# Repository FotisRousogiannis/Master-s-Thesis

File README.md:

# Master-s-Thesis
DEVELOPMENT OF ROBOTIC ARM AND INDEGRATION OF COMPUTER VISION METHODS

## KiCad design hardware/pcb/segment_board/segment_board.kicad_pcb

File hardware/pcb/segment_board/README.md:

# Segment board v1 (KiCad 10)

Κοινή πλακέτα τμήματος του βραχίονα — προδιαγραφή: [`SPEC.md`](SPEC.md), BOM/διαθεσιμότητα: [`bom/`](bom/).

## Άνοιγμα
Άνοιξε το `segment_board.kicad_pro` στο **KiCad 10** (το PCB είναι αποθηκευμένο σε μορφή KiCad 10· το σχηματικό παράγεται σε μορφή KiCad 7). **Κλείσε το KiCad πριν από `git pull`**, αλλιώς το KiCad ξαναγράφει τις παλιές ρυθμίσεις του project πάνω στις νέες.
Τα project libraries `segment_board` δηλώνονται στο `sym-lib-table` (σύμβολα, `lib/segment_board.kicad_sym`) και στο
`fp-lib-table` (footprints, `lib/segment_board.pretty`).

## Το σχηματικό παράγεται από κώδικα
Όλο το κύκλωμα ορίζεται στο `gen/build.py`. **Μην** αλλάζεις συνδέσεις στο KiCad — άλλαξε το `build.py` και ξαναπαράγε:
```bash
cd gen && python3 build.py
kicad-cli sch export netlist -o /tmp/board.net ../segment_board.kicad_sch && python3 check_netlist.py /tmp/board.net
```
Ελεύθερα στο KiCad: μετακίνηση/τακτοποίηση συμβόλων για αναγνωσιμότητα (θα χαθεί αν ξαναπαραχθεί), layout PCB.

| Φύλλο | Περιεχόμενο |
|---|---|
| `power` | XT30 7.4 V, ασφάλεια, προστασία πολικότητας, TVS, eFuse TPS259827, INA219 · MSTB 5.1 V, eFuse TPS259472A · ιδανικές δίοδοι, buck 3.3 V · LED τροφοδοσίας |
| `mcu` | ESP32-S3-WROOM-1, USB-C + ESD, RESET/BOOT, LED κατάστασης, header GPIO |
| `i2c` | jumpers επιλογής master, PCA9685, TCA9548A, ADS1115, pull-ups, header επέκτασης |
| `connectors` | 9 servo, 6 encoders, 2 αφής (MCV 3.5 mm), ανίχνευση σύνδεσης με LM339 + 17 LED |
| `pi_link` | header Raspberry Pi, UART/EN/BOOT Pi↔ESP32, RS-485 THVD1451 + LINK, οπές στερέωσης |

## Footprints του project (`gen/footprints.py` → `lib/segment_board.pretty`)
| Footprint | Εξάρτημα | Πηγή |
|---|---|---|
| `TI_RGE0024_2EP` | TPS259827 (VQFN-24 4×4, 2 thermal pads, θερμικά vias 0.2 mm) | TI RGE0024M land pattern (tps25982.pdf σ. 55–57) |
| `TI_RPW0010A` | TPS259472A (VQFN-HR-10 2×2, γωνιακά pads σε σχήμα L) | TI RPW0010A land pattern (tps25947.pdf σ. 72–74) |
| `L_4x4mm_SMNR4020` | πηνίο buck 2.2 µH 3.4 A (LCSC C135262) | land pattern LCSC |
| `RPi_Socket_2x20_FaceDown` | header Pi με **κατοπτρικές στήλες** (Pi ανάποδα) + περίγραμμα Pi 4/5 και οπές M2.5 στο User.Drawings | ίδιο με το `Raspberry_Pi_Zero_Socketed_THT_FaceDown` του KiCad |

## PCB (`segment_board.kicad_pcb`)
Δημιουργήθηκε με `python3 gen/pcb.py --force` (με **αυτόματη αρχική τοποθέτηση**: κάθε chip μαζί με τα μικρά εξαρτήματα που μοιράζονται σήμα μαζί του, ανά περιοχή) (δεν ξανατρέχει χωρίς `--force`, για να μη χαθεί δουλειά). Από εκεί
και πέρα το layout γίνεται στο KiCad. Αλλαγές του σχηματικού περνούν με **Tools → Update PCB from Schematic (F8)**.

- 100 × 120 mm, 4 στρώσεις: F.Cu σήματα · In1 **GND** (zone) · In2 τροφοδοσίες · B.Cu σήματα
- Κανόνες JLCPCB και net classes: `python3 gen/rules.py` (ασφαλές να ξανατρέξει)

  | Net class | Δίκτυα | Πλάτος | Γιατί |
  |---|---|---|---|
  | Power_Servo | `VS_*`, `VSERVO` | 2.5 mm (+ πολύγωνα) | έως ~10 A |
  | Servo_Ch | `SERVO*_GND` | 1.0 mm | επιστροφή servo, έως ~4 A στο μπλοκάρισμα |
  | Power_Logic | 5 V, 3.3 V, GND | 0.6 mm | |
  | Default | σήματα | 0.2 mm | |
- **Πρόταση τοποθέτησης** (μετακινείται ελεύθερα): connectors αριστερά σε 4 στήλες (έξω από το Pi, τα φις μπαίνουν
  από πάνω), Pi ανάποδα στο δεξί μισό με τις θύρες του στην κάτω άκρη, κεραία ESP32 στην πάνω άκρη (έξω από το Pi,
  με το keep-out του footprint), XT30 και MSTB στην πάνω άκρη, USB-C στη δεξιά άκρη. Τα υπόλοιπα εξαρτήματα είναι
  δίπλα στην πλακέτα, ομαδοποιημένα ανά φύλλο του σχηματικού.
- Κάτω από το Pi (≥ 18 mm ελεύθερο ύψος): μόνο SMD.
- Το CI (KiCad 10) τρέχει **DRC** με έλεγχο ισοτιμίας με το σχηματικό και βγάζει εικόνες της πλακέτας.

## Υλικά (`bom/`)
- `parts.csv`: κύρια εξαρτήματα · `passives.csv`: αντιστάσεις, πυκνωτές, LED κ.λπ. — επιλογή με `resolve_passives.py`
  (προτίμηση σε **basic** parts της JLC, χωρίς χρέωση setup). Το `build.py` βάζει τους κωδικούς LCSC στο σχηματικό.
- Χωρίς LCSC (κόλληση με το χέρι): connectors MCV/MSTB/XT30, header Pi, pin headers/jumpers, θήκη ασφάλειας.

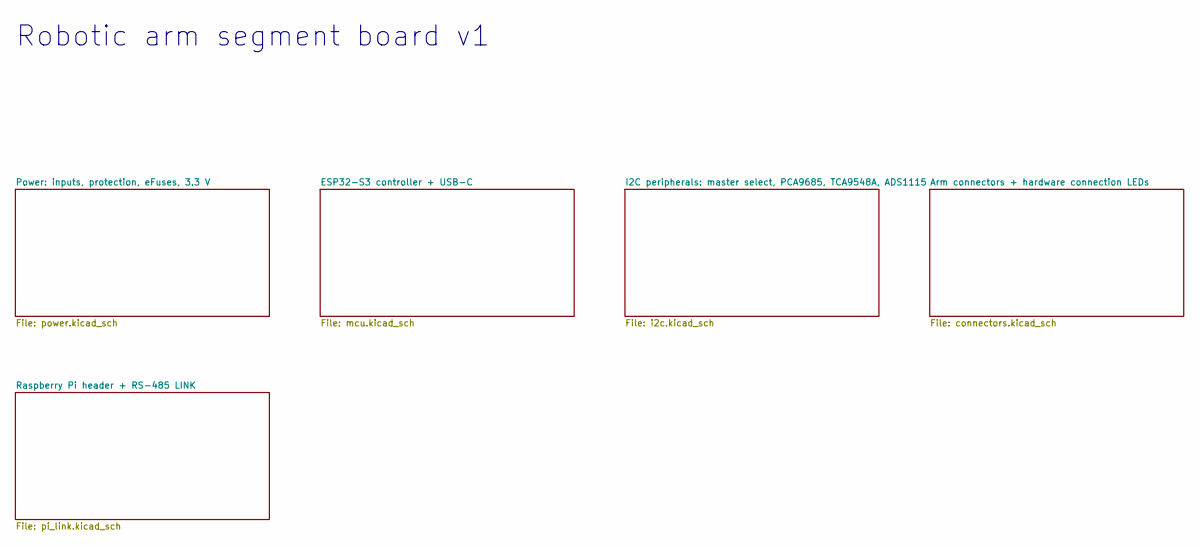
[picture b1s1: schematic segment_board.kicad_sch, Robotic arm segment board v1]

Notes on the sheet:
Robotic arm segment board v1

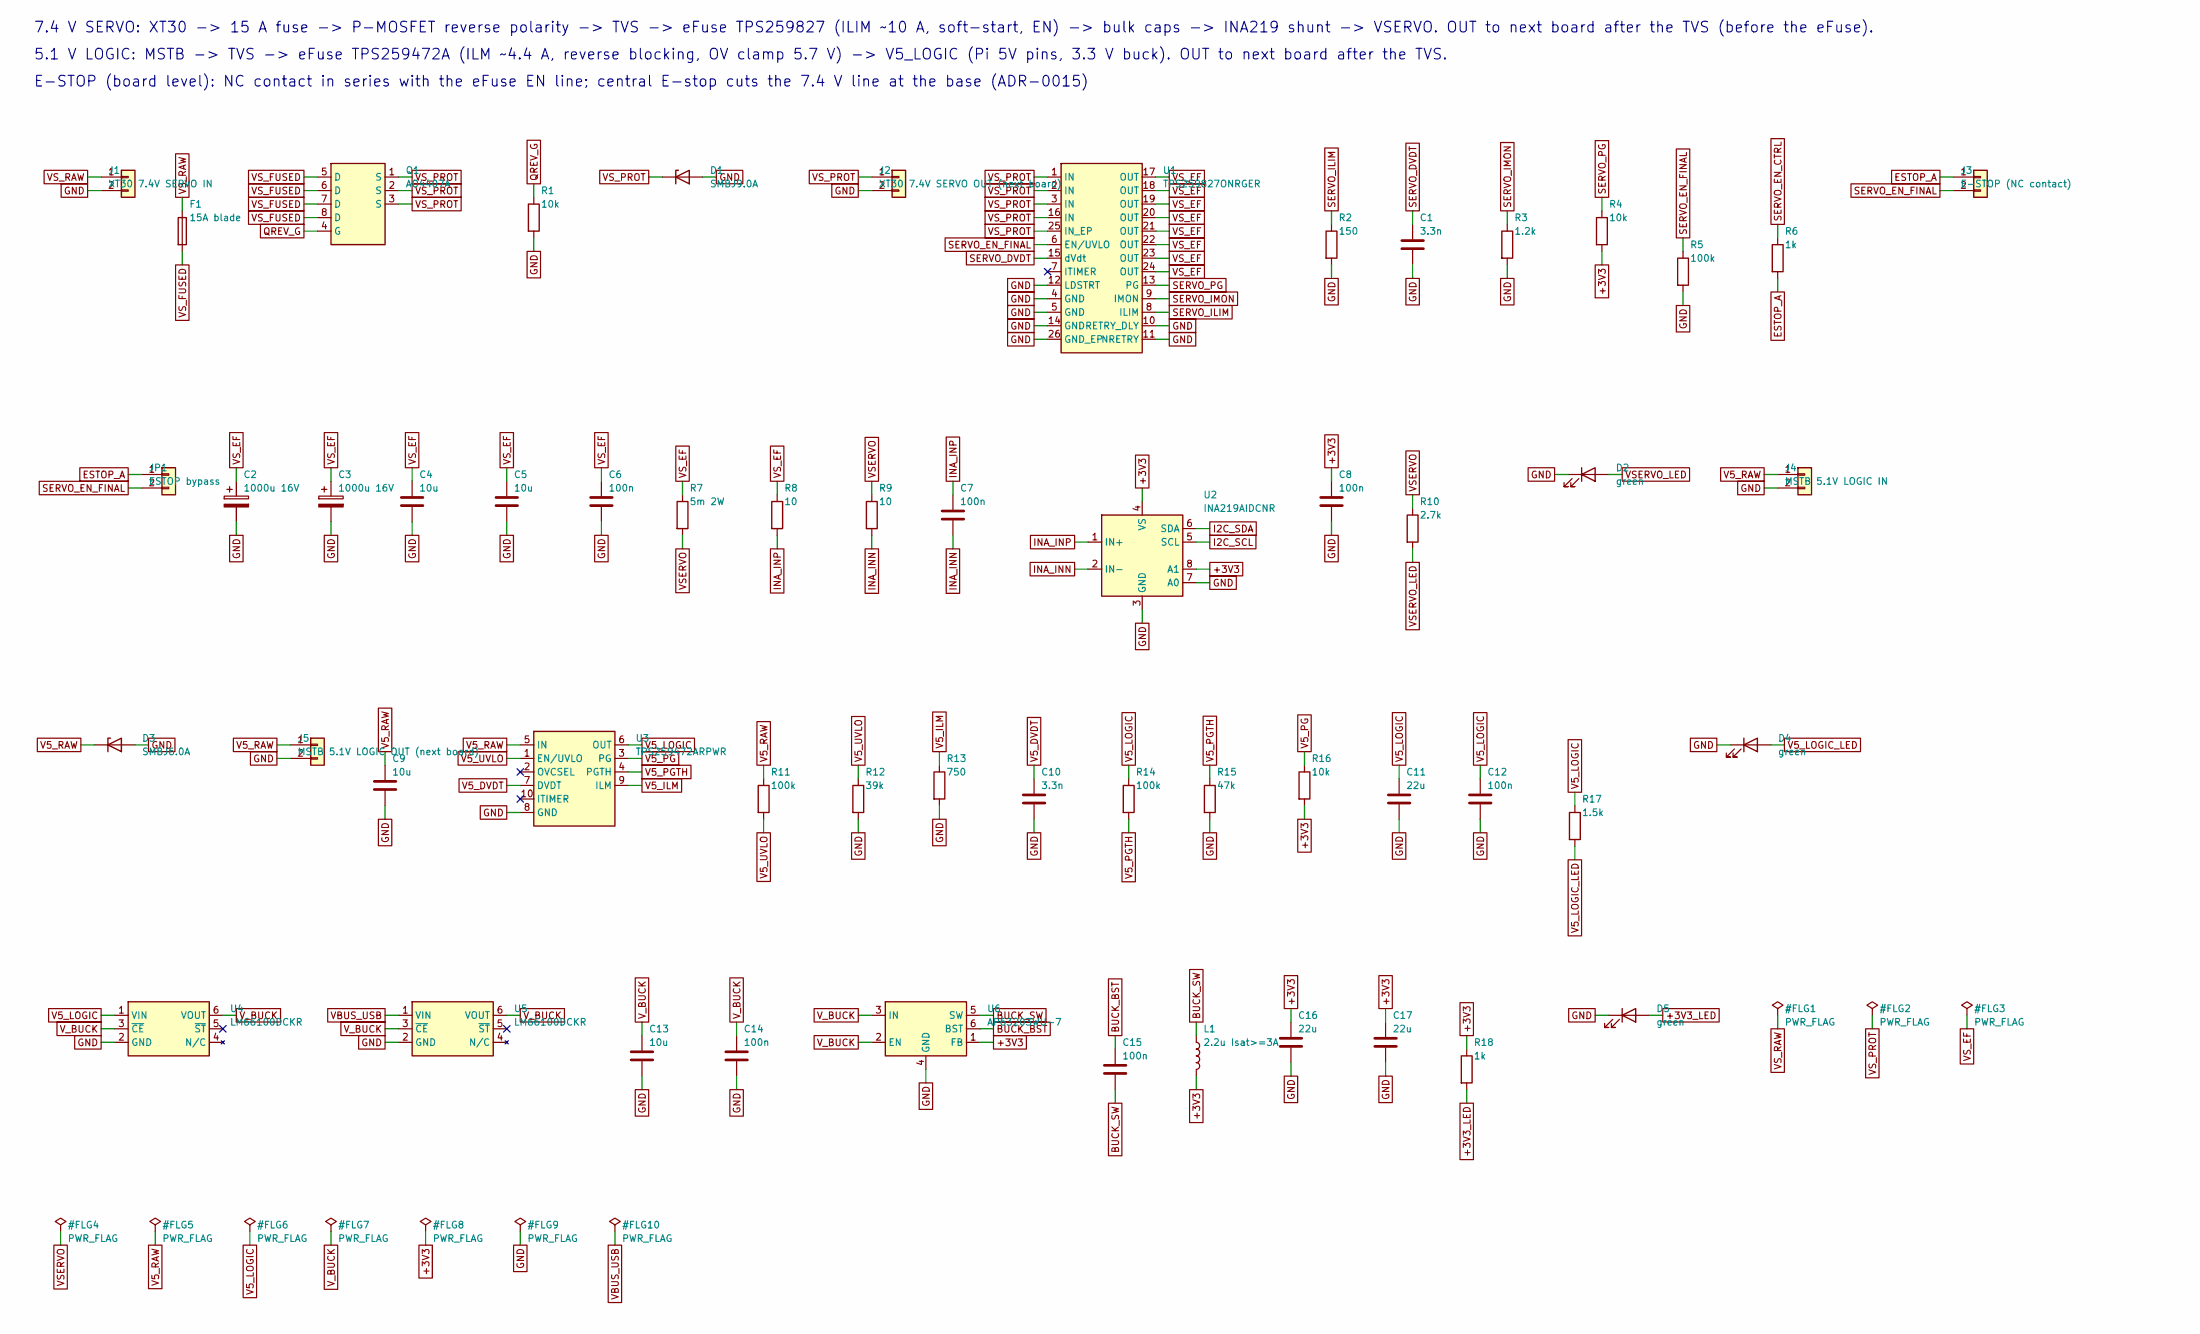
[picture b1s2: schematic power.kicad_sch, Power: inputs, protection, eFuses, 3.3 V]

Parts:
C1, C10: 3.3n; C_0402_1005Metric; LCSC C26404
C2, C3: 1000u 16V; CP_Radial_D10.0mm_P5.00mm; LCSC C88777
C4, C5, C9, C13: 10u; C_0805_2012Metric; LCSC C15850
C6, C7, C8, C12, C14, C15: 100n; C_0402_1005Metric; LCSC C1525
C11, C16, C17: 22u; C_0805_2012Metric; LCSC C45783
D1: SMBJ9.0A; D_SMB; LCSC C152088
D2, D4, D5: green; LED_0603_1608Metric; LCSC C2986030
D3: SMBJ6.0A; D_SMB; LCSC C19077560
F1: 15A blade; Fuseholder_Blade_Mini_Keystone_3568
J1: XT30 7.4V SERVO IN; AMASS_XT30PW-M_1x02_P2.50mm_Horizontal
J2: XT30 7.4V SERVO OUT (next board); AMASS_XT30UPB-F_1x02_P5.0mm_Vertical
J3: E-STOP (NC contact); PhoenixContact_MCV_1,5_2-G-3.5_1x02_P3.50mm_Vertical
J4: MSTB 5.1V LOGIC IN; PhoenixContact_MSTBVA_2,5_2-G-5,08_1x02_P5.08mm_Vertical
J5: MSTB 5.1V LOGIC OUT (next board); PhoenixContact_MSTBVA_2,5_2-G-5,08_1x02_P5.08mm_Vertical
JP1: ESTOP bypass; PinHeader_1x02_P2.54mm_Vertical
L1: 2.2u Isat>=3A; L_4x4mm_SMNR4020; LCSC C135262
Q1: AO4407A; SOIC-8_3.9x4.9mm_P1.27mm; LCSC C16072
R1, R4, R16: 10k; R_0402_1005Metric; LCSC C25744
R2: 150; R_0402_1005Metric; LCSC C25082
R3: 1.2k; R_0402_1005Metric; LCSC C25862
R5, R11, R14: 100k; R_0402_1005Metric; LCSC C25741
R6, R18: 1k; R_0402_1005Metric; LCSC C11702
R7: 5m 2W; R_2512_6332Metric; LCSC C371096
R8, R9: 10; R_0402_1005Metric; LCSC C25077
R10: 2.7k; R_0402_1005Metric; LCSC C25885
R12: 39k; R_0402_1005Metric; LCSC C25783
R13: 750; R_0402_1005Metric; LCSC C25132
R15: 47k; R_0402_1005Metric; LCSC C25792
R17: 1.5k; R_0402_1005Metric; LCSC C25867
U1: TPS259827ONRGER; TI_RGE0024_2EP; LCSC C2155761
U2: INA219AIDCNR; SOT-23-8; LCSC C87469
U3: TPS259472ARPWR; TI_RPW0010A; LCSC C3662789
U4, U5: LM66100DCKR; SOT-363_SC-70-6; LCSC C2869734
U6: AP63203WU-7; TSOT-23-6; LCSC C780769

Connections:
+3V3: C8.1, C16.1, C17.1, L1.2, R4.2, R16.2, R18.1, U2.4 (VS), U2.8 (A1), U6.1 (FB); also elsewhere on the board
+3V3_LED: D5.2 (A), R18.2
BUCK_BST: C15.1, U6.6 (BST)
BUCK_SW: C15.2, L1.1, U6.5 (SW)
ESTOP_A: J3.1, JP1.1, R6.2
GND: C1.2, C2.2, C3.2, C4.2, C5.2, C6.2, C8.2, C9.2, C10.2, C11.2, C12.2, C13.2, C14.2, C16.2, C17.2, D1.2 (A), D2.1 (K), D3.2 (A), D4.1 (K), D5.1 (K), J1.2, J2.2, J4.2, J5.2, R1.2, R2.2, R3.2, R5.2, R12.2, R13.2, R15.2, U1.4 (GND), U1.5 (GND), U1.10 (RETRY_DLY), U1.11 (NRETRY), U1.12 (LDSTRT), U1.14 (GND), U1.26 (GND_EP), U2.3 (GND), U2.7 (A0), U3.8 (GND), U4.2 (GND), U5.2 (GND), U6.4 (GND); also elsewhere on the board
I2C_SCL: U2.5 (SCL); also elsewhere on the board
I2C_SDA: U2.6 (SDA); also elsewhere on the board
INA_INN: C7.2, R9.2, U2.2 (IN-)
INA_INP: C7.1, R8.2, U2.1 (IN+)
QREV_G: Q1.4 (G), R1.1
SERVO_DVDT: C1.1, U1.15 (dVdt)
SERVO_EN_CTRL: R6.1; also elsewhere on the board
SERVO_EN_FINAL: J3.2, JP1.2, R5.1, U1.6 (EN/UVLO)
SERVO_ILIM: R2.1, U1.8 (ILIM)
SERVO_IMON: R3.1, U1.9 (IMON); also elsewhere on the board
SERVO_PG: R4.1, U1.13 (PG); also elsewhere on the board
V5_DVDT: C10.1, U3.7 (DVDT)
V5_ILM: R13.1, U3.9 (ILM)
V5_LOGIC: C11.1, C12.1, R14.1, R17.1, U3.6 (OUT), U4.1 (VIN); also elsewhere on the board
V5_LOGIC_LED: D4.2 (A), R17.2
V5_PG: R16.1, U3.3 (PG); also elsewhere on the board
V5_PGTH: R14.2, R15.1, U3.4 (PGTH)
V5_RAW: C9.1, D3.1 (K), J4.1, J5.1, R11.1, U3.5 (IN)
V5_UVLO: R11.2, R12.1, U3.1 (EN/UVLO)
VBUS_USB: U5.1 (VIN); also elsewhere on the board
VSERVO: R7.2, R9.1, R10.1; also elsewhere on the board
VSERVO_LED: D2.2 (A), R10.2
VS_EF: C2.1, C3.1, C4.1, C5.1, C6.1, R7.1, R8.1, U1.17 (OUT), U1.18 (OUT), U1.19 (OUT), U1.20 (OUT), U1.21 (OUT), U1.22 (OUT), U1.23 (OUT), U1.24 (OUT)
VS_FUSED: F1.2, Q1.5 (D), Q1.6 (D), Q1.7 (D), Q1.8 (D)
VS_PROT: D1.1 (K), J2.1, Q1.1 (S), Q1.2 (S), Q1.3 (S), U1.1 (IN), U1.2 (IN), U1.3 (IN), U1.16 (IN), U1.25 (IN_EP)
VS_RAW: F1.1, J1.1
V_BUCK: C13.1, C14.1, U4.3 (~CE), U4.6 (VOUT), U5.3 (~CE), U5.6 (VOUT), U6.2 (EN), U6.3 (IN)

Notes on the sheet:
7.4 V SERVO: XT30 -> 15 A fuse -> P-MOSFET reverse polarity -> TVS -> eFuse TPS259827 (ILIM ~10 A, soft-start, EN) -> bulk caps -> INA219 shunt -> VSERVO. OUT to next board after the TVS (before the eFuse).
5.1 V LOGIC: MSTB -> TVS -> eFuse TPS259472A (ILM ~4.4 A, reverse blocking, OV clamp 5.7 V) -> V5_LOGIC (Pi 5V pins, 3.3 V buck). OUT to next board after the TVS.
E-STOP (board level): NC contact in series with the eFuse EN line; central E-stop cuts the 7.4 V line at the base (ADR-0015)

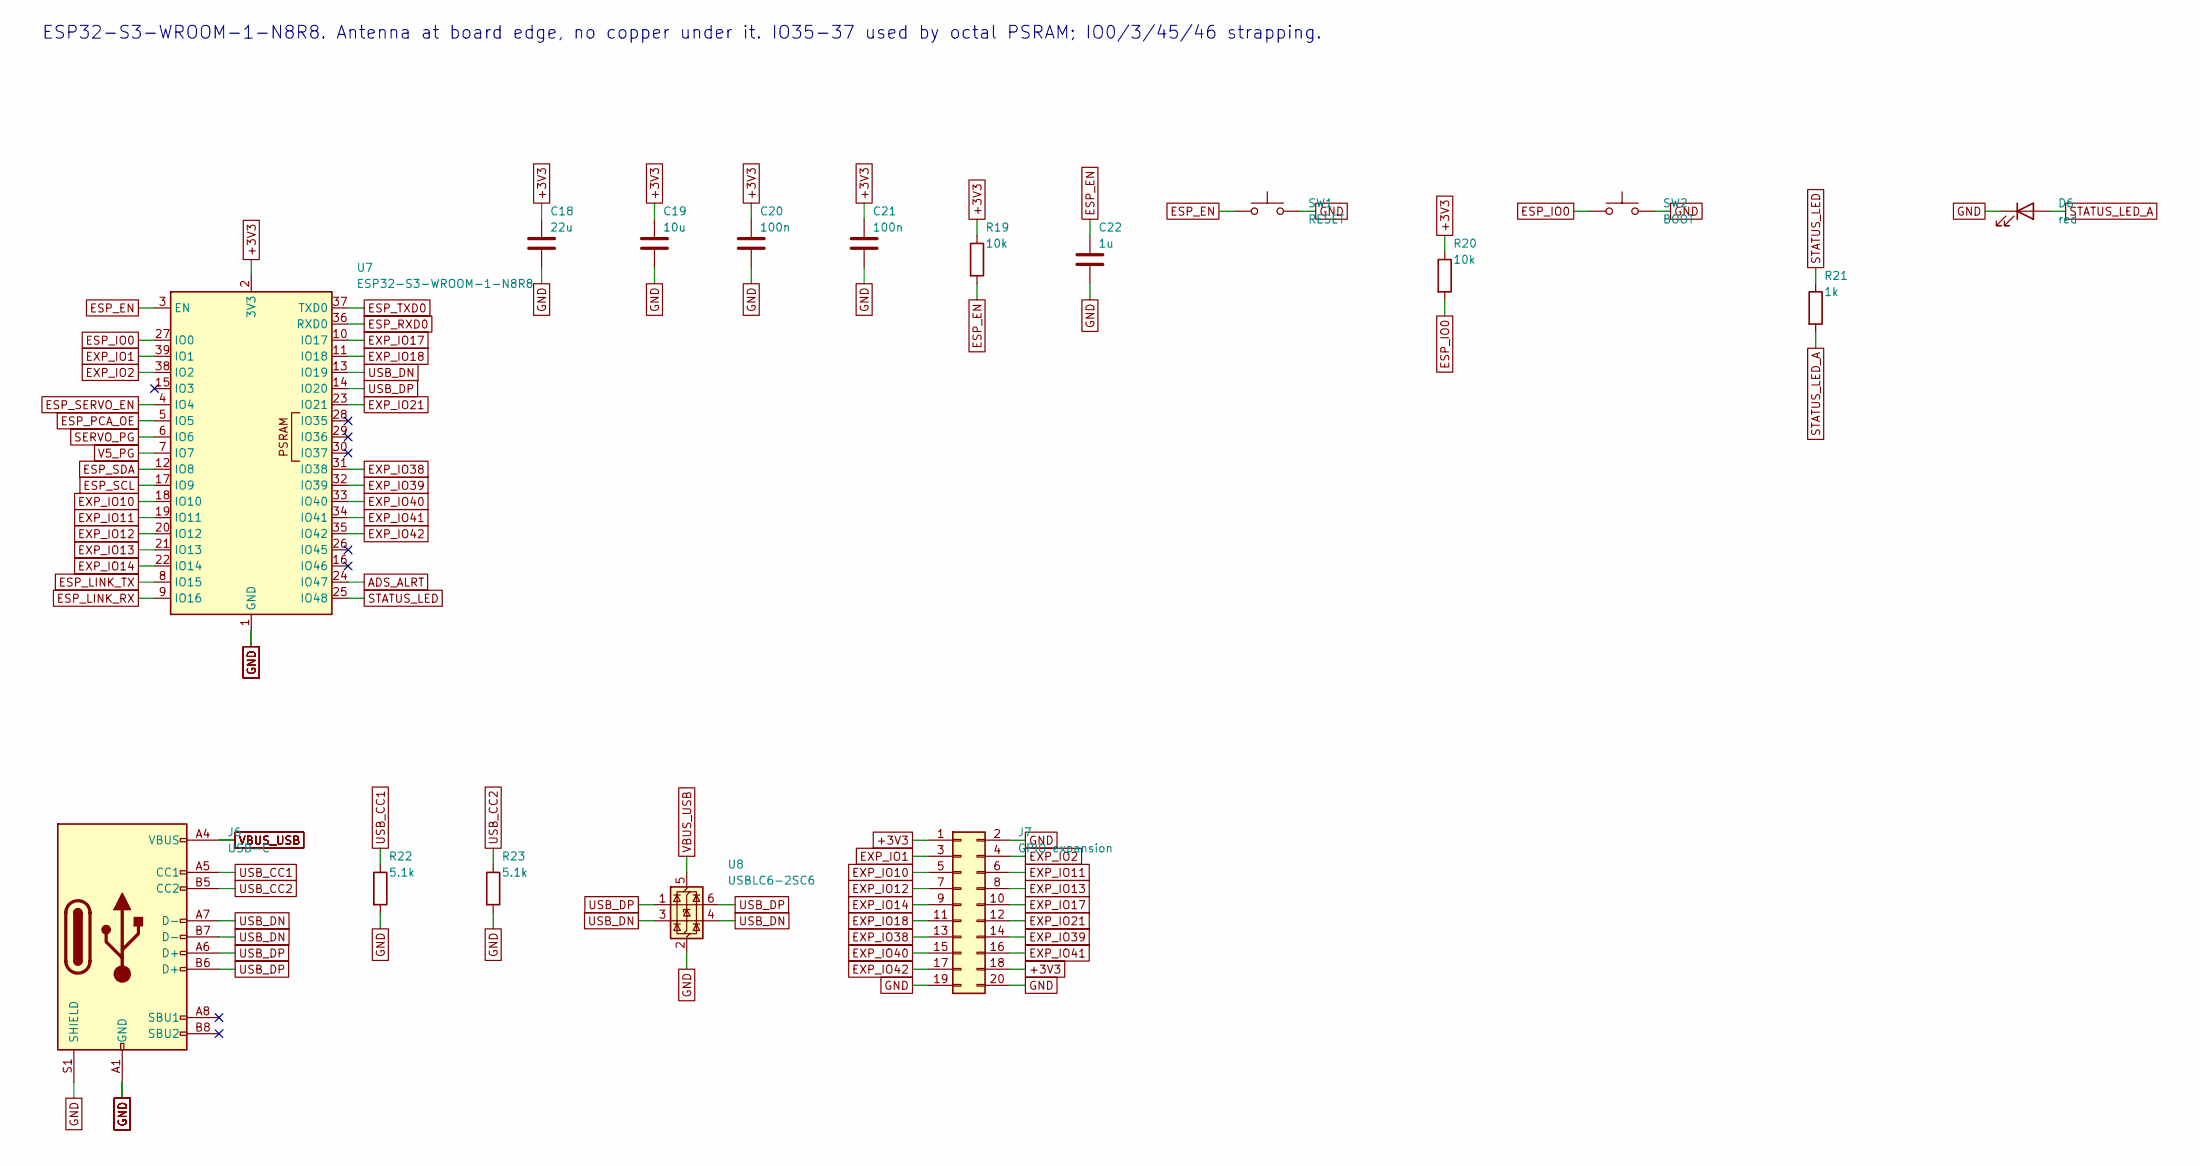
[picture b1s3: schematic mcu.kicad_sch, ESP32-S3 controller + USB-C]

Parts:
C18: 22u; C_0805_2012Metric; LCSC C45783
C19: 10u; C_0805_2012Metric; LCSC C15850
C20, C21: 100n; C_0402_1005Metric; LCSC C1525
C22: 1u; C_0402_1005Metric; LCSC C52923
D6: red; LED_0603_1608Metric; LCSC C2986060
J6: USB-C; USB_C_Receptacle_HRO_TYPE-C-31-M-12_S1; LCSC C165948
J7: GPIO expansion; PinHeader_2x10_P2.54mm_Vertical
R19, R20: 10k; R_0402_1005Metric; LCSC C25744
R21: 1k; R_0402_1005Metric; LCSC C11702
R22, R23: 5.1k; R_0402_1005Metric; LCSC C25905
SW1: RESET; SW_SPST_TL3342; LCSC C2886897
SW2: BOOT; SW_SPST_TL3342; LCSC C2886897
U7: ESP32-S3-WROOM-1-N8R8; ESP32-S3-WROOM-1; LCSC C2913201
U8: USBLC6-2SC6; SOT-23-6; LCSC C7519

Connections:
+3V3: C18.1, C19.1, C20.1, C21.1, J7.1, J7.18, R19.1, R20.1, U7.2 (3V3); also elsewhere on the board
ADS_ALRT: U7.24 (IO47); also elsewhere on the board
ESP_EN: C22.1, R19.2, SW1.1, U7.3 (EN); also elsewhere on the board
ESP_IO0: R20.2, SW2.1, U7.27 (IO0); also elsewhere on the board
ESP_LINK_RX: U7.9 (IO16); also elsewhere on the board
ESP_LINK_TX: U7.8 (IO15); also elsewhere on the board
ESP_PCA_OE: U7.5 (IO5); also elsewhere on the board
ESP_RXD0: U7.36 (RXD0); also elsewhere on the board
ESP_SCL: U7.17 (IO9); also elsewhere on the board
ESP_SDA: U7.12 (IO8); also elsewhere on the board
ESP_SERVO_EN: U7.4 (IO4); also elsewhere on the board
ESP_TXD0: U7.37 (TXD0); also elsewhere on the board
EXP_IO1: J7.3, U7.39 (IO1)
EXP_IO2: J7.4, U7.38 (IO2)
EXP_IO10: J7.5, U7.18 (IO10)
EXP_IO11: J7.6, U7.19 (IO11)
EXP_IO12: J7.7, U7.20 (IO12)
EXP_IO13: J7.8, U7.21 (IO13)
EXP_IO14: J7.9, U7.22 (IO14)
EXP_IO17: J7.10, U7.10 (IO17)
EXP_IO18: J7.11, U7.11 (IO18)
EXP_IO21: J7.12, U7.23 (IO21)
EXP_IO38: J7.13, U7.31 (IO38)
EXP_IO39: J7.14, U7.32 (IO39)
EXP_IO40: J7.15, U7.33 (IO40)
EXP_IO41: J7.16, U7.34 (IO41)
EXP_IO42: J7.17, U7.35 (IO42)
GND: C18.2, C19.2, C20.2, C21.2, C22.2, D6.1 (K), J6.A1 (GND), J6.A12 (GND), J6.B1 (GND), J6.B12 (GND), J6.S1 (SHIELD), J7.2, J7.19, J7.20, R22.2, R23.2, SW1.2, SW2.2, U7.1 (GND), U7.40 (GND), U7.41 (GND), U8.2 (GND); also elsewhere on the board
SERVO_PG: U7.6 (IO6); also elsewhere on the board
STATUS_LED: R21.1, U7.25 (IO48)
STATUS_LED_A: D6.2 (A), R21.2
USB_CC1: J6.A5 (CC1), R22.1
USB_CC2: J6.B5 (CC2), R23.1
USB_DN: J6.A7 (D-), J6.B7 (D-), U7.13 (IO19), U8.3 (I/O2), U8.4 (I/O2)
USB_DP: J6.A6 (D+), J6.B6 (D+), U7.14 (IO20), U8.1 (I/O1), U8.6 (I/O1)
V5_PG: U7.7 (IO7); also elsewhere on the board
VBUS_USB: J6.A4 (VBUS), J6.A9 (VBUS), J6.B4 (VBUS), J6.B9 (VBUS), U8.5 (VBUS); also elsewhere on the board

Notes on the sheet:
ESP32-S3-WROOM-1-N8R8. Antenna at board edge, no copper under it. IO35-37 used by octal PSRAM; IO0/3/45/46 strapping.

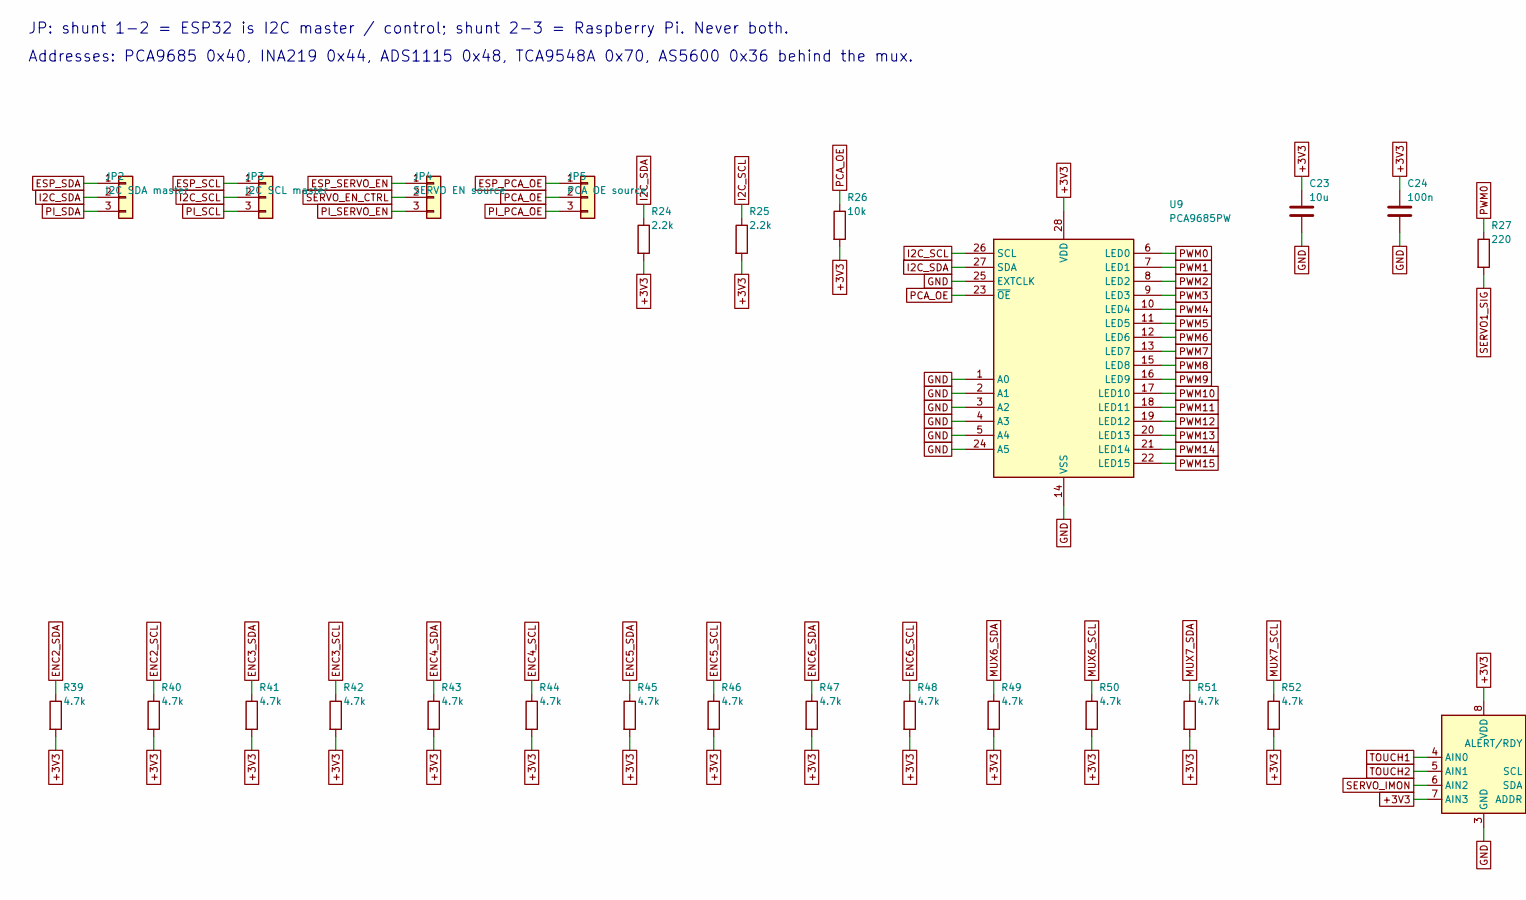
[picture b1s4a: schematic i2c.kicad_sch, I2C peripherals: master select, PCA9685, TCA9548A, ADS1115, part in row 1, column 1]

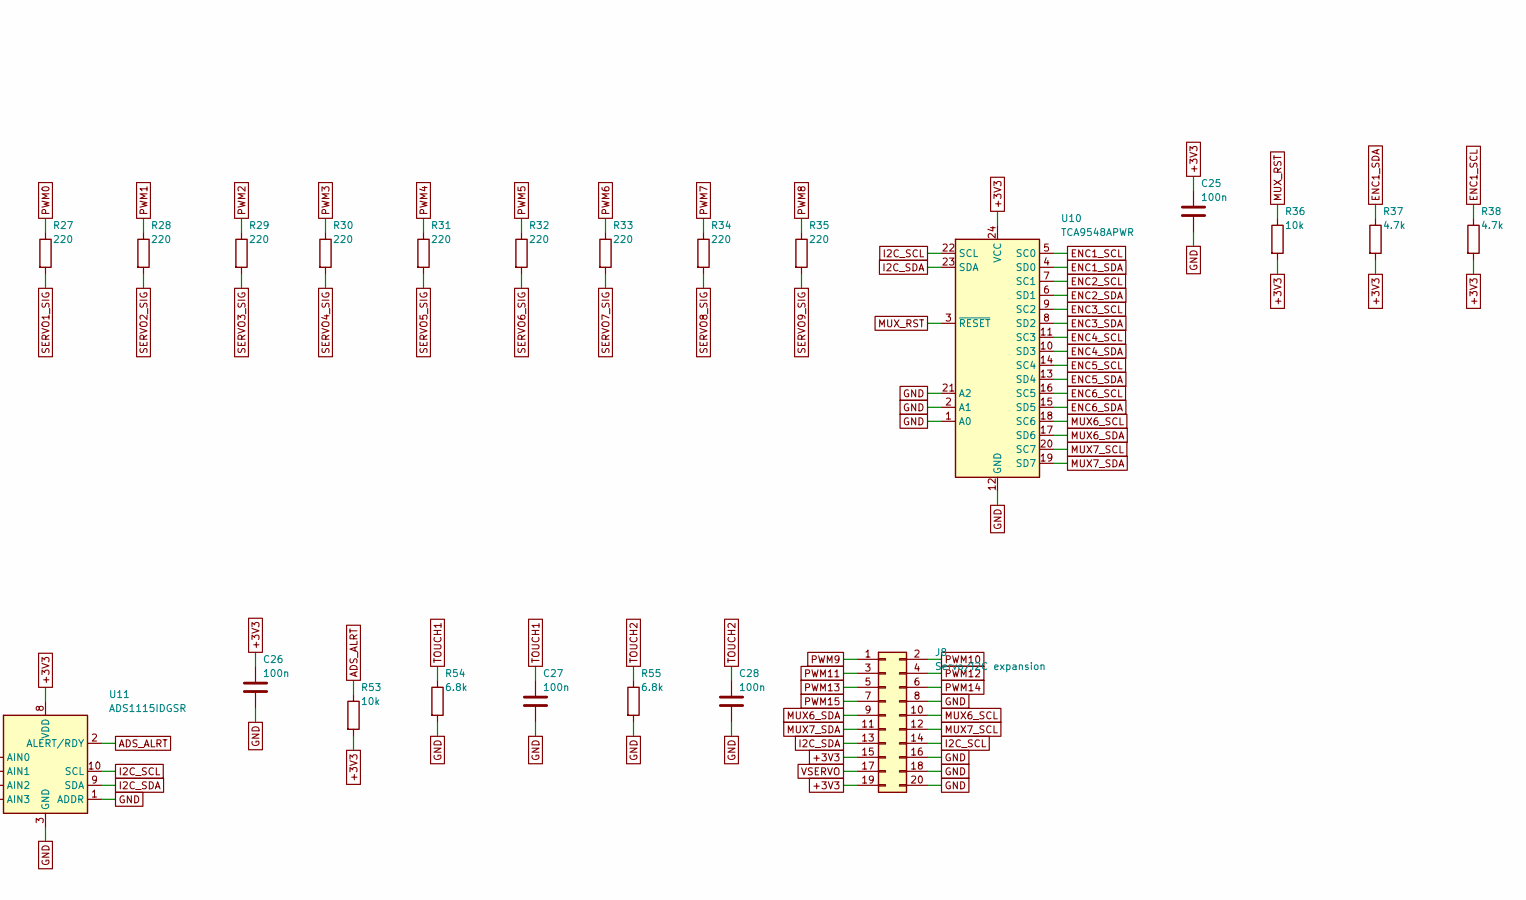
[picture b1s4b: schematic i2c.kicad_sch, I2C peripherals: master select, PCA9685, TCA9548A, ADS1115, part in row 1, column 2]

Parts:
C23: 10u; C_0805_2012Metric; LCSC C15850
C24, C25, C26, C27, C28: 100n; C_0402_1005Metric; LCSC C1525
J8: Servo/I2C expansion; PinHeader_2x10_P2.54mm_Vertical
JP2: I2C SDA master; PinHeader_1x03_P2.54mm_Vertical
JP3: I2C SCL master; PinHeader_1x03_P2.54mm_Vertical
JP4: SERVO EN source; PinHeader_1x03_P2.54mm_Vertical
JP5: PCA OE source; PinHeader_1x03_P2.54mm_Vertical
R24, R25: 2.2k; R_0402_1005Metric; LCSC C25879
R26, R36, R53: 10k; R_0402_1005Metric; LCSC C25744
R27, R28, R29, R30, R31, R32, R33, R34, R35: 220; R_0402_1005Metric; LCSC C25091
R37, R38, R39, R40, R41, R42, R43, R44, R45, R46, R47, R48, R49, R50, R51, R52: 4.7k; R_0402_1005Metric; LCSC C25900
R54, R55: 6.8k; R_0402_1005Metric; LCSC C25917
U9: PCA9685PW; TSSOP-28_4.4x9.7mm_P0.65mm; LCSC C2678753
U10: TCA9548APWR; TSSOP-24_4.4x7.8mm_P0.65mm; LCSC C130026
U11: ADS1115IDGSR; VSSOP-10_3x3mm_P0.5mm; LCSC C37593

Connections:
+3V3: C23.1, C24.1, C25.1, C26.1, J8.15, J8.19, R24.2, R25.2, R26.2, R36.2, R37.2, R38.2, R39.2, R40.2, R41.2, R42.2, R43.2, R44.2, R45.2, R46.2, R47.2, R48.2, R49.2, R50.2, R51.2, R52.2, R53.2, U9.28 (VDD), U10.24 (VCC), U11.7 (AIN3), U11.8 (VDD); also elsewhere on the board
ADS_ALRT: R53.1, U11.2 (ALERT/RDY); also elsewhere on the board
ENC1_SCL: R38.1, U10.5 (SC0); also elsewhere on the board
ENC1_SDA: R37.1, U10.4 (SD0); also elsewhere on the board
ENC2_SCL: R40.1, U10.7 (SC1); also elsewhere on the board
ENC2_SDA: R39.1, U10.6 (SD1); also elsewhere on the board
ENC3_SCL: R42.1, U10.9 (SC2); also elsewhere on the board
ENC3_SDA: R41.1, U10.8 (SD2); also elsewhere on the board
ENC4_SCL: R44.1, U10.11 (SC3); also elsewhere on the board
ENC4_SDA: R43.1, U10.10 (SD3); also elsewhere on the board
ENC5_SCL: R46.1, U10.14 (SC4); also elsewhere on the board
ENC5_SDA: R45.1, U10.13 (SD4); also elsewhere on the board
ENC6_SCL: R48.1, U10.16 (SC5); also elsewhere on the board
ENC6_SDA: R47.1, U10.15 (SD5); also elsewhere on the board
ESP_PCA_OE: JP5.1; also elsewhere on the board
ESP_SCL: JP3.1; also elsewhere on the board
ESP_SDA: JP2.1; also elsewhere on the board
ESP_SERVO_EN: JP4.1; also elsewhere on the board
GND: C23.2, C24.2, C25.2, C26.2, C27.2, C28.2, J8.8, J8.16, J8.18, J8.20, R54.2, R55.2, U9.1 (A0), U9.2 (A1), U9.3 (A2), U9.4 (A3), U9.5 (A4), U9.14 (VSS), U9.24 (A5), U9.25 (EXTCLK), U10.1 (A0), U10.2 (A1), U10.12 (GND), U10.21 (A2), U11.1 (ADDR), U11.3 (GND); also elsewhere on the board
I2C_SCL: J8.14, JP3.2, R25.1, U9.26 (SCL), U10.22 (SCL), U11.10 (SCL); also elsewhere on the board
I2C_SDA: J8.13, JP2.2, R24.1, U9.27 (SDA), U10.23 (SDA), U11.9 (SDA); also elsewhere on the board
MUX6_SCL: J8.10, R50.1, U10.18 (SC6)
MUX6_SDA: J8.9, R49.1, U10.17 (SD6)
MUX7_SCL: J8.12, R52.1, U10.20 (SC7)
MUX7_SDA: J8.11, R51.1, U10.19 (SD7)
MUX_RST: R36.1, U10.3 (~RESET)
PCA_OE: JP5.2, R26.1, U9.23 (~OE)
PI_PCA_OE: JP5.3; also elsewhere on the board
PI_SCL: JP3.3; also elsewhere on the board
PI_SDA: JP2.3; also elsewhere on the board
PI_SERVO_EN: JP4.3; also elsewhere on the board
PWM0: R27.1, U9.6 (LED0)
PWM1: R28.1, U9.7 (LED1)
PWM2: R29.1, U9.8 (LED2)
PWM3: R30.1, U9.9 (LED3)
PWM4: R31.1, U9.10 (LED4)
PWM5: R32.1, U9.11 (LED5)
PWM6: R33.1, U9.12 (LED6)
PWM7: R34.1, U9.13 (LED7)
PWM8: R35.1, U9.15 (LED8)
PWM9: J8.1, U9.16 (LED9)
PWM10: J8.2, U9.17 (LED10)
PWM11: J8.3, U9.18 (LED11)
PWM12: J8.4, U9.19 (LED12)
PWM13: J8.5, U9.20 (LED13)
PWM14: J8.6, U9.21 (LED14)
PWM15: J8.7, U9.22 (LED15)
SERVO1_SIG: R27.2; also elsewhere on the board
SERVO2_SIG: R28.2; also elsewhere on the board
SERVO3_SIG: R29.2; also elsewhere on the board
SERVO4_SIG: R30.2; also elsewhere on the board
SERVO5_SIG: R31.2; also elsewhere on the board
SERVO6_SIG: R32.2; also elsewhere on the board
SERVO7_SIG: R33.2; also elsewhere on the board
SERVO8_SIG: R34.2; also elsewhere on the board
SERVO9_SIG: R35.2; also elsewhere on the board
SERVO_EN_CTRL: JP4.2; also elsewhere on the board
SERVO_IMON: U11.6 (AIN2); also elsewhere on the board
TOUCH1: C27.1, R54.1, U11.4 (AIN0); also elsewhere on the board
TOUCH2: C28.1, R55.1, U11.5 (AIN1); also elsewhere on the board
VSERVO: J8.17; also elsewhere on the board

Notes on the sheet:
JP: shunt 1-2 = ESP32 is I2C master / control; shunt 2-3 = Raspberry Pi. Never both.
Addresses: PCA9685 0x40, INA219 0x44, ADS1115 0x48, TCA9548A 0x70, AS5600 0x36 behind the mux.
